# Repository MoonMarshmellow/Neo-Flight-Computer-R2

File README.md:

## NEO Flight Computer Schematics
These are the schematics for the NEO dual deploy flight computer.

### Features
- IMU For inertial positioning and acceleration data.
- Barometer for barometric altitude.
- 2 Pyrotechnic channels for charge deployment.
- Support for up to 12V Powersupply.
- Intergrated Flash Storage and SD Card for Data logging (optional)
- Battery Voltage Reader
- Almost all components are through-hole soldered for ease of assembly without solder paste.
- Support for various adafruit IMUs or Barometers.
- Small footprint (55x100mm) to keep manufacturing cheap.
- LED/Buzzer for output
- I2C/SPI Expansion Slots

### Main components:
Full BOM is in the repo.
- Arduino NANO processor (widely available and easily programmable, low memory so libraries that can be used are limited (can be used with the Nano Every, which has more memory))
- Adafruit BMP388 breakout board (compatible with almost all adafruit Barometer boards)
- Adafruit ICM20649 IMU (compatible with almost all adafruit IMU boards)
- Micro SD card socket
- W25Q32FV Winbond Flash Storage Chip (compatible with other similar pinout chips like the SST25VF064C from Microchip)

### Firmware
Firmware for the board is a work in progress, but the board is compatible with all main Arduino Libraries for each sensor and the SD and Flash Chip. Writing simple software for launch and apogee detection isn't too difficult.

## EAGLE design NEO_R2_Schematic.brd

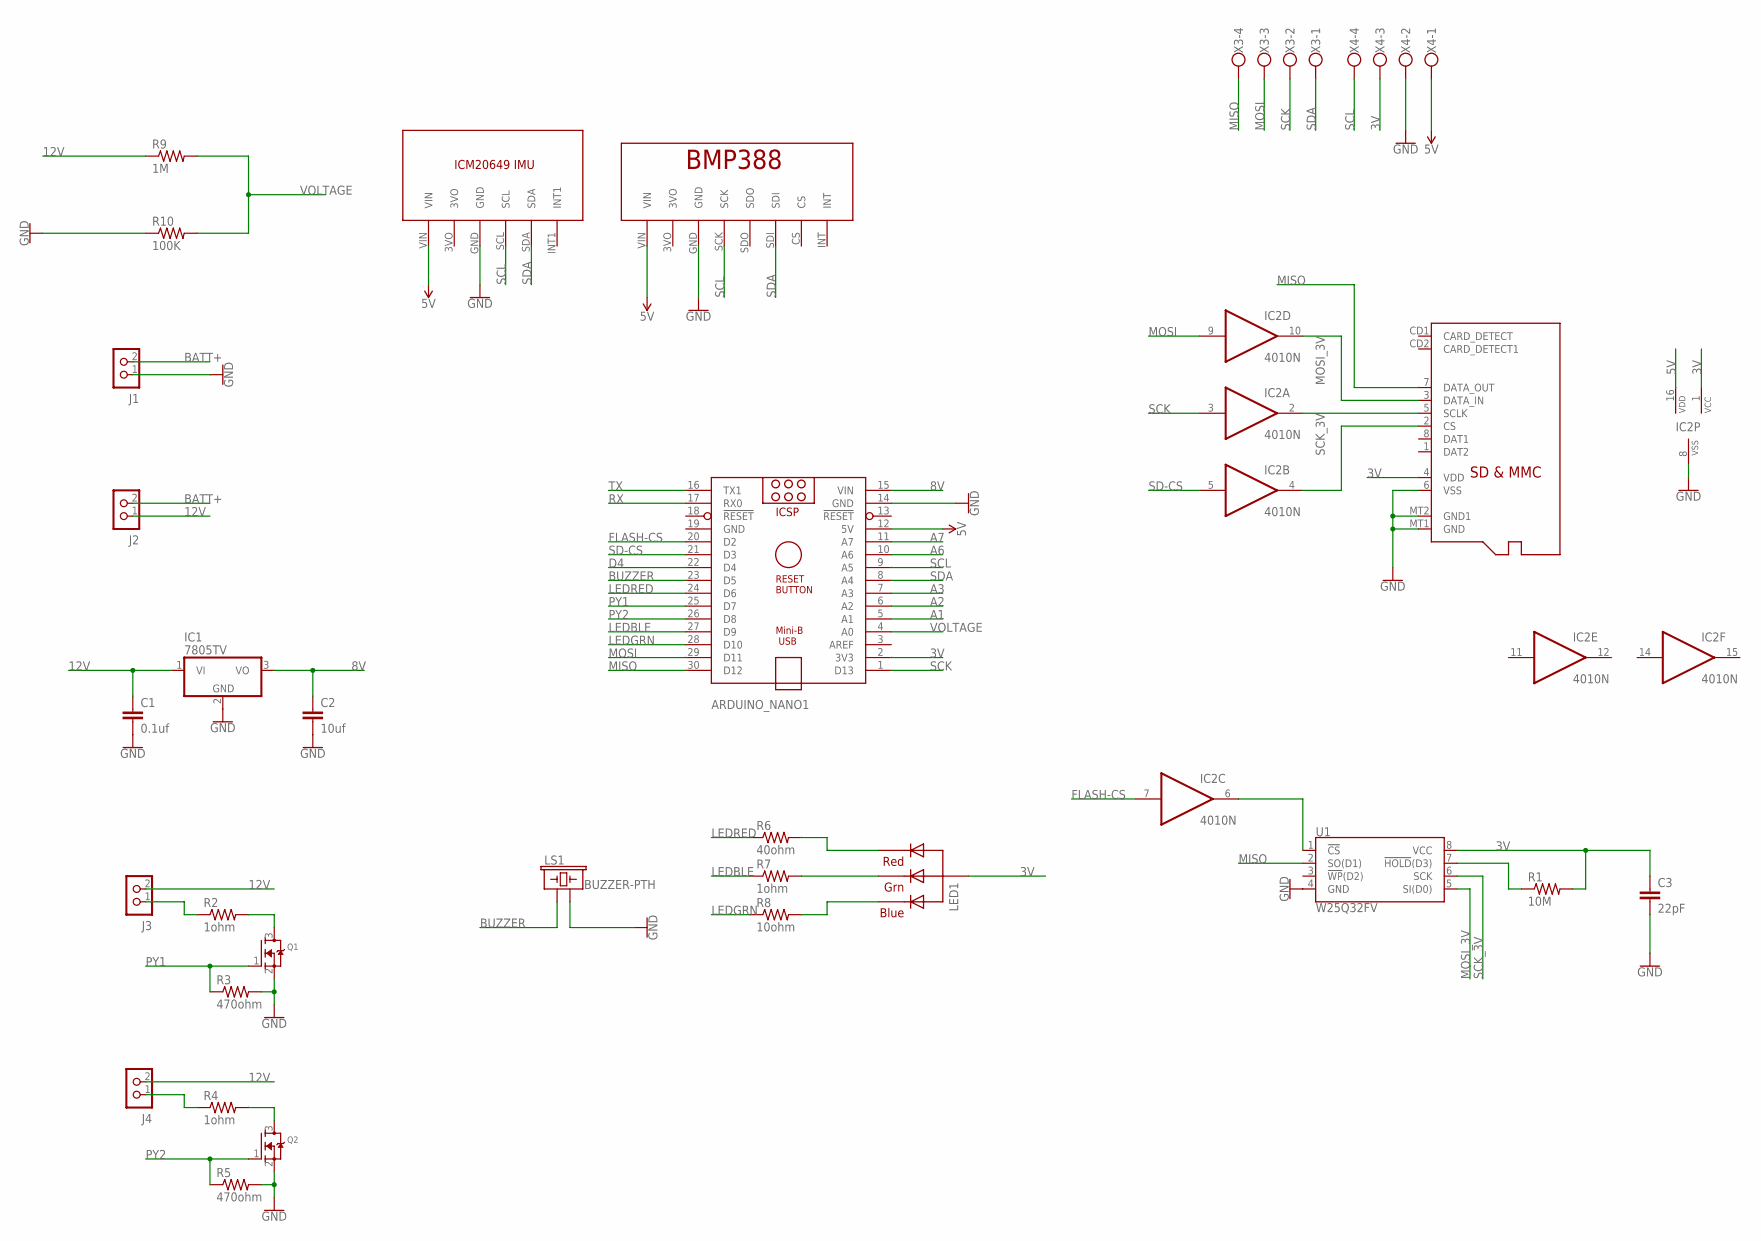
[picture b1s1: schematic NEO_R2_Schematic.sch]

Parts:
ARDUINO_NANO1: ARDUINO_NANO
C1: 0.1uf; C025-024X044
C2: 10uf; C025-024X044
C3: 22pF; C025-024X044
IC1: 7805TV; TO220V
IC2: 4010N; DIL16
J1, J2, J3, J4: CON_TERMINAL_BLOCK_02-5MM; TERMINAL_BLOCK_2P_5
LED1: RGBLED_CA-5MM; LED5MMRGB
LS1: BUZZER-PTH; BUZZER-12MM
Q1, Q2: MOSFET-NREFLOW; SOT23
R1: 10M; 0207/7
R2, R4, R7: 1ohm; 0207/7
R3, R5: 470ohm; 0207/7
R6: 40ohm; 0207/7
R8: 10ohm; 0207/7
R9: 1M; 0207/7
R10: 100K; 0207/7
U1: W25Q32FV; SOIC-8
U$1: MICROSD
U$3: BMP388
U$4: ICM20649
X3, X4: W237-4

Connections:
3V: ARDUINO_NANO1.2 (3V3), C3.1, IC2.1 (VCC), LED1.2 (VCC), R1.2, U1.8 (VCC), U$1.4 (VDD), X4.3
5V: ARDUINO_NANO1.12 (5V), IC2.16 (VDD), U$3.VIN, U$4.VIN, X4.1
8V: ARDUINO_NANO1.15 (VIN), C2.1, IC1.3 (VO)
12V: C1.1, IC1.1 (VI), J2.1, J3.2, J4.2, R9.1
A1: ARDUINO_NANO1.5 (A1)
A2: ARDUINO_NANO1.6 (A2)
A3: ARDUINO_NANO1.7 (A3)
A6: ARDUINO_NANO1.10 (A6)
A7: ARDUINO_NANO1.11 (A7)
BATT+: J1.2, J2.2
BUZZER: ARDUINO_NANO1.23 (D5), LS1.+ (1)
D4: ARDUINO_NANO1.22 (D4)
FLASH-CS: ARDUINO_NANO1.20 (D2), IC2.7 (I)
GND: ARDUINO_NANO1.14 (GND), ARDUINO_NANO1.19 (GND), C1.2, C2.2, C3.2, IC1.2 (GND), IC2.8 (VSS), J1.1, LS1.- (2), Q1.2 (S), Q2.2 (S), R3.2, R5.2, R10.1, U1.4 (GND), U$1.6 (VSS), U$1.MT1 (GND), U$1.MT2 (GND1), U$3.GND, U$4.GND, X4.2
LEDBLE: ARDUINO_NANO1.27 (D9), R7.1
LEDGRN: ARDUINO_NANO1.28 (D10), R8.1
LEDRED: ARDUINO_NANO1.24 (D6), R6.1
MISO: ARDUINO_NANO1.30 (D12), U1.2 (SO(D1)), U$1.7 (DATA_OUT), X3.4
MOSI: ARDUINO_NANO1.29 (D11), IC2.9 (I), X3.3
MOSI_3V: IC2.10 (O), U1.5 (SI(D0)), U$1.3 (DATA_IN)
unnamed: R1.1, U1.7 (!HOLD!(D3))
unnamed: J3.1, R2.1
unnamed: Q1.3 (D), R2.2
unnamed: J4.1, R4.1
unnamed: Q2.3 (D), R4.2
unnamed: IC2.4 (O), U$1.2 (CS)
unnamed: LED1.1 (RED), R6.2
unnamed: LED1.3 (GREEN), R7.2
unnamed: LED1.4 (BLUE), R8.2
unnamed: IC2.6 (O), U1.1 (!CS!)
PY1: ARDUINO_NANO1.25 (D7), Q1.1 (G), R3.1
PY2: ARDUINO_NANO1.26 (D8), Q2.1 (G), R5.1
RX: ARDUINO_NANO1.17 (RX0)
SCK: ARDUINO_NANO1.1 (D13), IC2.3 (I), X3.2
SCK_3V: IC2.2 (O), U1.6 (SCK), U$1.5 (SCLK)
SCL: ARDUINO_NANO1.9 (A5), U$3.SCK, U$4.SCL, X4.4
SD-CS: ARDUINO_NANO1.21 (D3), IC2.5 (I)
SDA: ARDUINO_NANO1.8 (A4), U$3.SDI, U$4.SDA, X3.1
TX: ARDUINO_NANO1.16 (TX1)
VOLTAGE: ARDUINO_NANO1.4 (A0), R9.2, R10.2

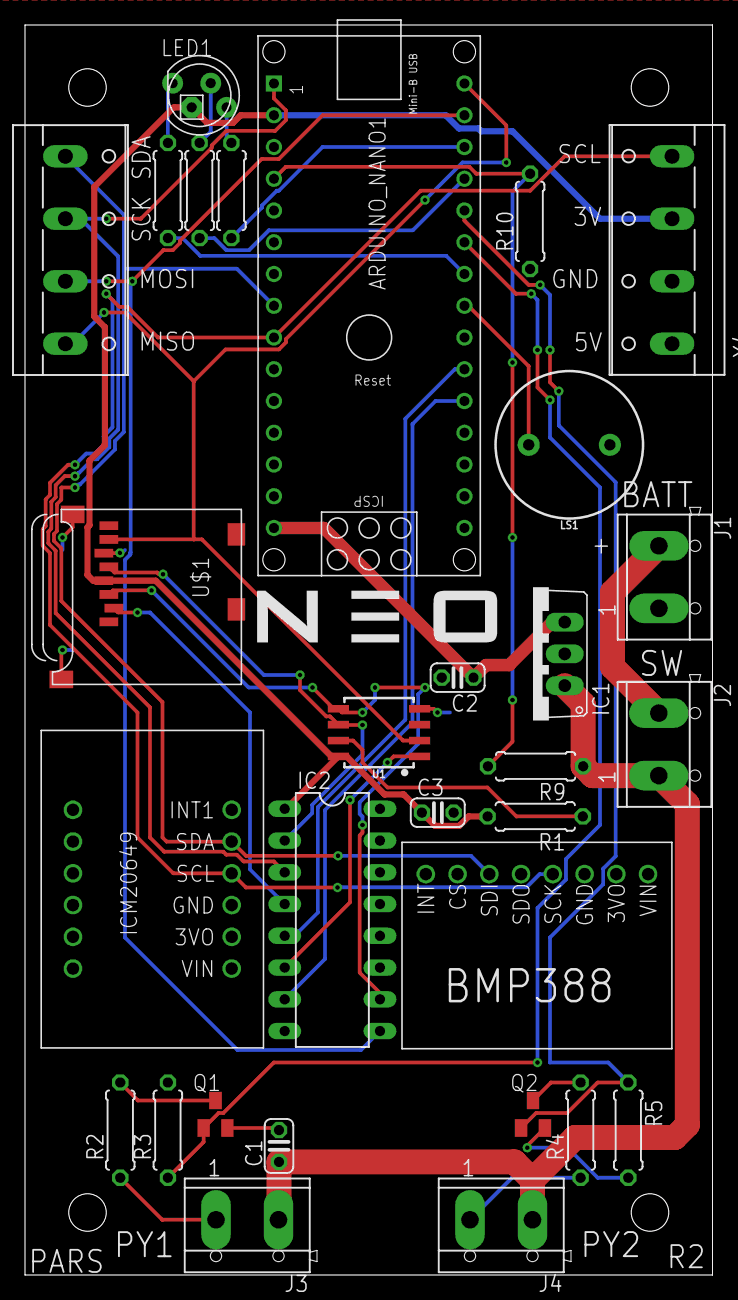
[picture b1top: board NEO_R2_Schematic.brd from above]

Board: 2 copper layers, 55.0 x 100.0 mm, 30 parts (0 on the bottom side), 32 nets.

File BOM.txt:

Partlist exported from C:/Users/katzi/Documents/EAGLE/projects/NEO_R2/Inceptor_Schematic.sch at 24/02/2024 13:05

Qty Value                     Device                    Package             Parts          Description                                                MF MPN OC_FARNELL OC_NEWARK POPULARITY PROD_ID    SF_SKU    SPICEPREFIX VALUE   
1                             ARDUINO_NANO              ARDUINO_NANO        ARDUINO_NANO1  Arduino Nano V3.0                                                                                                                          
2                             MOSFET-NREFLOW            SOT23               Q1, Q2         N-Channel Mosfet                                                                                                                           
2                             W237-4                    W237-4              X3, X4         WAGO SCREW CLAMP                                                  unknown    unknown   10                                                  
1   0.1uf                     C-EU025-024X044           C025-024X044        C1             CAPACITOR, European symbol                                                             56                              C                   
1   100K                      R-US_0207/7               0207/7              R10            RESISTOR, American symbol                                                                                                                  
1   10M                       R-US_0207/7               0207/7              R1             RESISTOR, American symbol                                                                                                                  
1   10ohm                     R-US_0207/7               0207/7              R8             RESISTOR, American symbol                                                                                                                  
1   10uf                      C-EU025-024X044           C025-024X044        C2             CAPACITOR, European symbol                                                             56                              C                   
1   1M                        R-US_0207/7               0207/7              R9             RESISTOR, American symbol                                                                                                                  
3   1ohm                      R-US_0207/7               0207/7              R2, R4, R7     RESISTOR, American symbol                                                                                                                  
1   22pF                      C-EU025-024X044           C025-024X044        C3             CAPACITOR, European symbol                                                             56                              C                   
1   4010N                     4010N                     DIL16               IC2            Hex BUFFER, Non-inverting                                                              0                                                   
1   40ohm                     R-US_0207/7               0207/7              R6             RESISTOR, American symbol                                                                                                                  
2   470ohm                    R-US_0207/7               0207/7              R3, R5         RESISTOR, American symbol                                                                                                                  
1   7805TV                    7805TV                    TO220V              IC1            Positive VOLTAGE REGULATOR                                                             57                                                  
1   BMP388                    BMP388                    BMP388              U$3                                                                                                                                                       
1   BUZZER-PTH                BUZZER-PTH                BUZZER-12MM         LS1            Buzzer                                                                                            COMP-08253 COM-07950                     
4   CON_TERMINAL_BLOCK_02-5MM CON_TERMINAL_BLOCK_02-5MM TERMINAL_BLOCK_2P_5 J1, J2, J3, J4 2 poles wire to board terminal block                                                                                                       
1   ICM20649                  ICM20649                  ICM20649            U$4                                                                                                                                                       
1   MICROSD                   MICROSD                   MICROSD             U$1            Micro-SD / Transflash card holder with SPI pinout                                                                                          
1   RGBLED_CA-5MM             RGBLED_CA-5MM             LED5MMRGB           LED1           RGB LED, common-anode5MM Staggered pins5mm Piranha package                                                                                 
1   W25Q32FV                  W25Q32FVSS                SOIC-8              U1             W25Q32FV 32Mb (4MB) Serial Flash Memory                                                           IC-13229                         W25Q32FV

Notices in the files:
parts and their libraries:
SparkFun-Electromechanical: Licensing: Creative Commons ShareAlike 4.0 International - https://creativecommons.org/licenses/by-sa/4.0
40xx: Source: www.fairchildsemi.com CD4010.pdf  © 2000 Fairchild Semiconductor Corporation DS005945
